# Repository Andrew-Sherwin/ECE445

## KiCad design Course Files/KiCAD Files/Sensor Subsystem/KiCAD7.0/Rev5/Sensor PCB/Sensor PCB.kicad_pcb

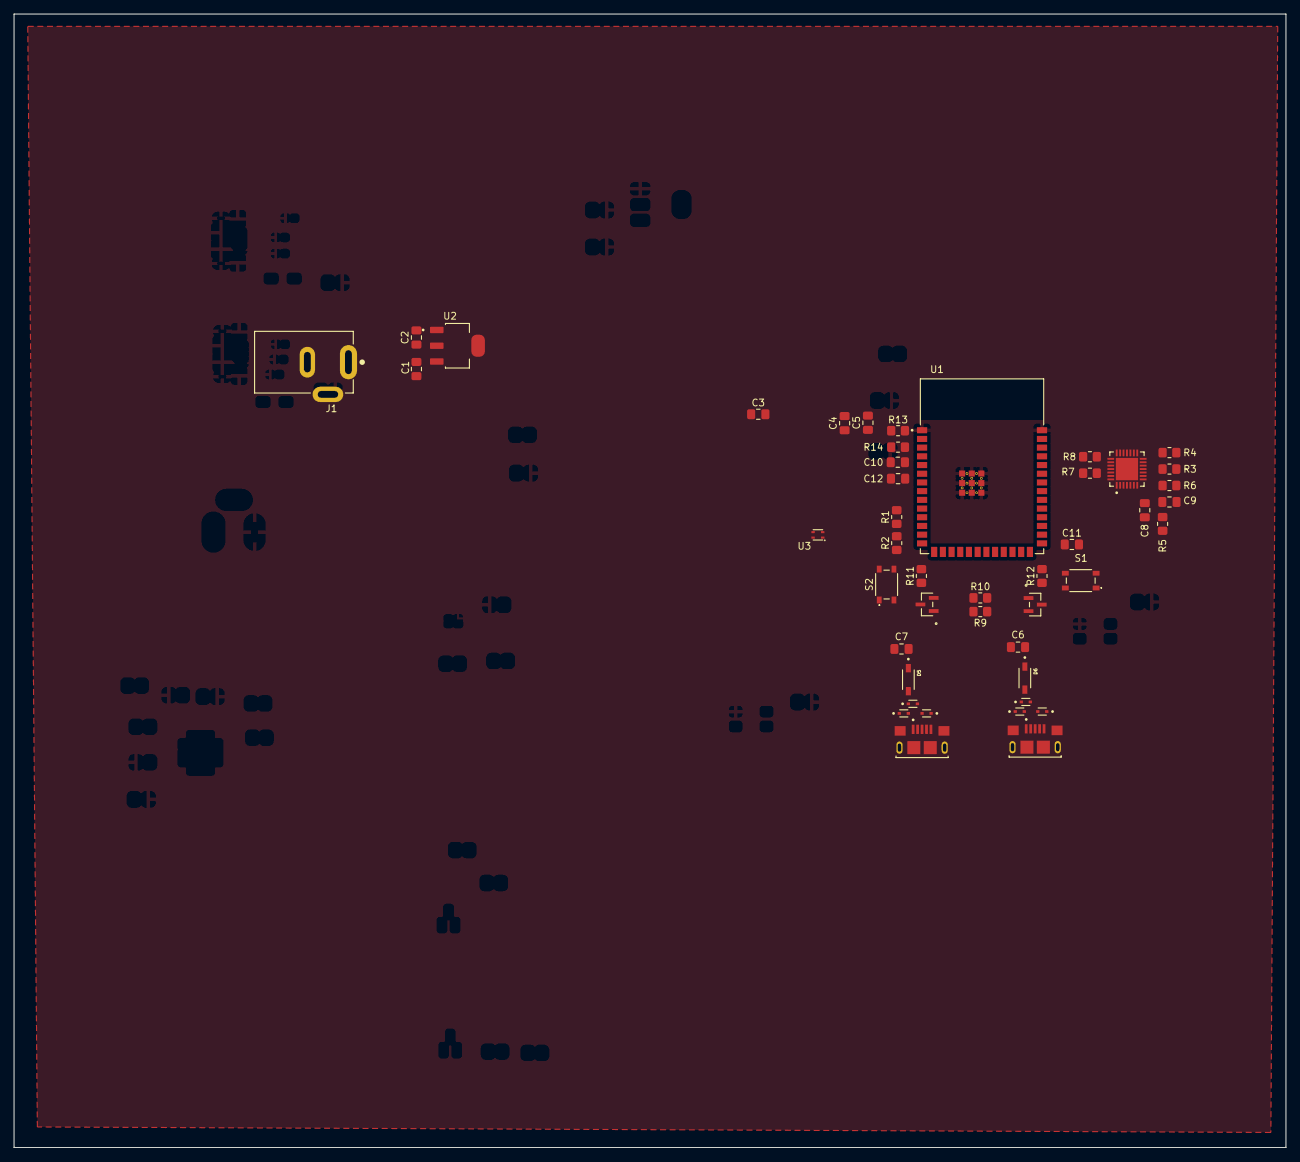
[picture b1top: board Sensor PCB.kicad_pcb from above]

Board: 2 copper layers, 185.6 x 165.4 mm, 45 parts (0 on the bottom side), 28 nets, no tracks yet.

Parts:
C1, C9, C10: 1uF; C_0805_2012Metric_Pad1.18x1.45mm_HandSolder
C2: 4.7uF; C_0805_2012Metric_Pad1.18x1.45mm_HandSolder
C3: 100nF; C_0805_2012Metric_Pad1.18x1.45mm_HandSolder
C4, C6, C7, C8: 10uF; C_0805_2012Metric_Pad1.18x1.45mm_HandSolder
C5, C11, C12: 0.1uF; C_0805_2012Metric_Pad1.18x1.45mm_HandSolder
D1, D2, D3, D4, D7, D8: LESD5D5.0CT1G; LESD5D5_0CT1G
D5, D6: 1N5819HW-7-F
J1: PJ-202AH
J2, J3: 10118193-0001LF
R1, R2, R4, R9, R10, R14: 10000; R_0805_2012Metric_Pad1.20x1.40mm_HandSolder
R3: 1000; R_0805_2012Metric_Pad1.20x1.40mm_HandSolder
R5: 22100; R_0805_2012Metric_Pad1.20x1.40mm_HandSolder
R6: 47500; R_0805_2012Metric_Pad1.20x1.40mm_HandSolder
R7, R8, R11, R12, R13: 0; R_0805_2012Metric_Pad1.20x1.40mm_HandSolder
S1, S2: PTS815_SJG_250_SMTR_LFS; PTS815 SJG 250 SMTR LFS
U1: ESP32-S3-WROOM-1-N8; ESP32-S3-WROOM-1-N8-SnapEDA
U2: LDL1117S33R-SnapEDA
U3: SHT45-AD1B-R3
U4: CP2102N-A02-GQFN28
U5, U6: L8050QLT1G; SOT-23_ONS

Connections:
+3.3V: C2.1, C3.2, C4.1, C5.1, C8.1, R1.2, R2.2, R3.1, R13.2, U2.2 (VOUT), U2.4 (VOUT), U3.3 (VDD), U4.6 (VDD), U4.7 (VREGIN)
+12V: C1.1, J1.1, U2.3 (VIN)
CHIP_PU: C10.1, C12.1, R11.2, R14.2, S2.4 (NO), U1.3 (EN)
DTR: R9.1, U4.28 (DTR), U6.2 (EMITTER)
ESP_3V3: R13.1, R14.1, U1.2 (3V3)
GND: C1.2, C2.2, C3.1, C4.2, C5.2, C6.2, C7.2, C8.2, C9.2, C10.2, C11.2, C12.2, D1.1, D2.1, D3.1, D4.1, D7.1, D8.1, J1.2, J2.5 (GND), J2.S1 (SHIELD), J2.S2 (SHIELD__1), J2.S3 (SHIELD__2), J2.S4 (SHIELD__3), J2.S5 (SHIELD__4), J2.S6 (SHIELD__5), J3.5 (GND), J3.S1 (SHIELD), J3.S2 (SHIELD__1), J3.S3 (SHIELD__2), J3.S4 (SHIELD__3), J3.S5 (SHIELD__4), J3.S6 (SHIELD__5), R4.1, R6.1, S1.1 (COM), S2.1 (COM), U1.1 (GND), U1.40 (GND), U1.41_1 (GND), U1.41_2 (GND), U1.41_3 (GND), U1.41_4 (GND), U1.41_5 (GND), U1.41_6 (GND), U1.41_7 (GND), U1.41_8 (GND), U1.41_9 (GND), U2.1 (GND), U3.4 (VSS), U4.3 (GND), U4.29 (GND__1)
IO0: C11.1, R12.2, S1.4 (NO), U1.27 (IO0)
IO19: D4.2, J3.2 (D-), U1.13 (IO19)
IO20: D3.2, J3.3 (D+), U1.14 (IO20)
unnamed: C6.1, D6.C
unnamed: C7.1, D5.C
unnamed: R1.1, U1.12 (IO8), U3.1 (SDA)
unnamed: R2.1, U1.17 (IO9), U3.2 (SCL)
unnamed: R8.1, U4.25 (RXD)
unnamed: R7.1, U4.26 (TXD)
unnamed: C9.1, R5.2, R6.2, U4.8 (VBUS)
unnamed: R3.2, U4.9 (~RST)
unnamed: R4.2, U4.11 (~SUSPEND)
unnamed: R9.2, U5.1 (BASE)
unnamed: R11.1, U5.3 (COLLECTOR)
unnamed: R10.2, U6.1 (BASE)
unnamed: R12.1, U6.3 (COLLECTOR)
RTS: R10.1, U4.24 (RTS), U5.2 (EMITTER)
U0RXD: R7.2, U1.36 (RXD0)
U0TXD: R8.2, U1.37 (TXD0)
USB_DN: D2.2, J2.2 (D-), U4.5 (D-)
USB_DP: D1.2, J2.3 (D+), U4.4 (D+)
VBUS: D5.A, D6.A, D7.2, D8.2, J2.1 (VUSB), J3.1 (VUSB), R5.1

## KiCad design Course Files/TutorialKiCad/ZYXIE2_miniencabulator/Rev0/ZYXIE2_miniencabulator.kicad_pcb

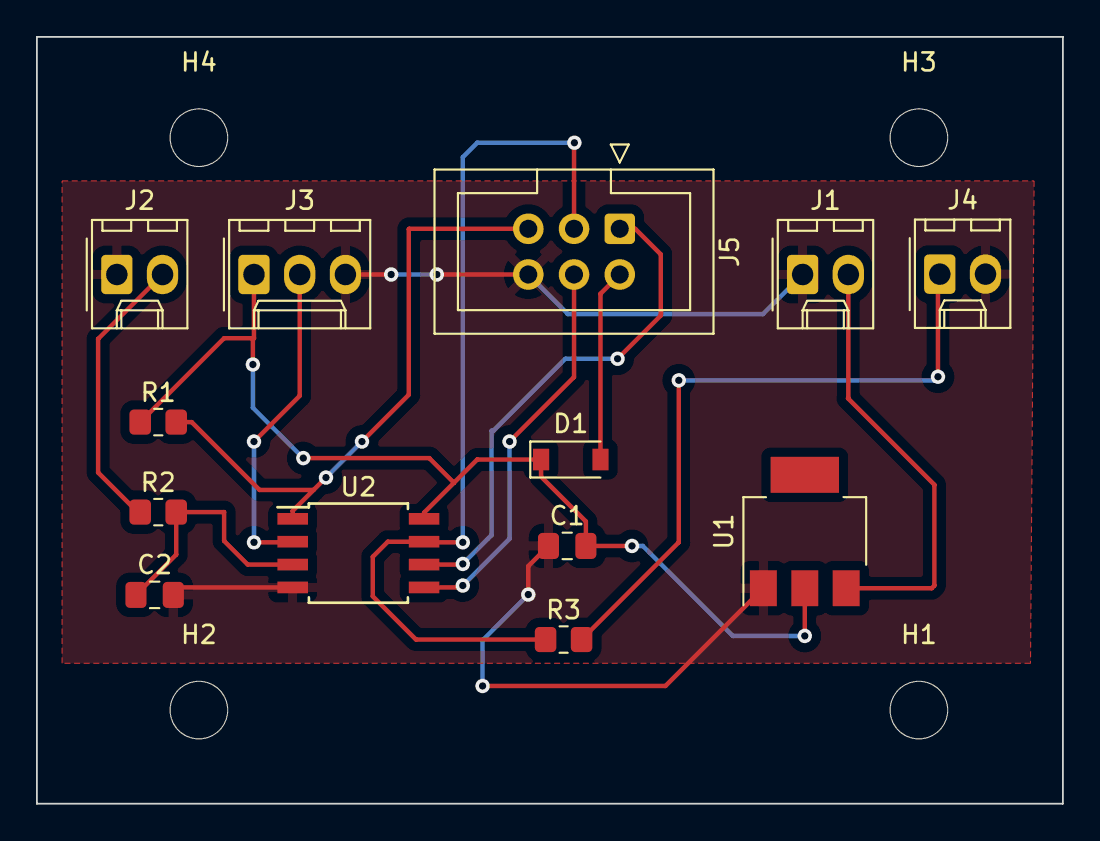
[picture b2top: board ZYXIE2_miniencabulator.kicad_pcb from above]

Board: 2 copper layers, 57.0 x 42.6 mm, 17 parts (0 on the bottom side), 12 nets.

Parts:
C1, C2: 1uF; C_0805_2012Metric_Pad1.18x1.45mm_HandSolder
D1: MBR0520; D_SOD-123
H1, H2, H3, H4: MountingHole; MountingHole_3.2mm_M3
J1: Vin; Molex_KK-254_AE-6410-02A_1x02_P2.54mm_Vertical
J2: BUTTON; Molex_KK-254_AE-6410-02A_1x02_P2.54mm_Vertical
J3: POT; Molex_KK-254_AE-6410-03A_1x03_P2.54mm_Vertical
J4: LED; Molex_KK-254_AE-6410-02A_1x02_P2.54mm_Vertical
J5: AVR-ISP-6; IDC-Header_2x03_P2.54mm_Vertical
R1, R2: 10000; R_0805_2012Metric_Pad1.20x1.40mm_HandSolder
R3: 1000; R_0805_2012Metric_Pad1.20x1.40mm_HandSolder
U1: LM1117-5.0; SOT-223
U2: ATtiny85-20S; SOIC-8W_5.3x5.3mm_P1.27mm

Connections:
+5V: C1.2, D1.1 (K), J3.1, R1.1, U1.2 (VO), U2.8 (VCC)
/MISO: J5.1 (MISO), U2.6 (PB1)
/MOSI: J5.4 (MOSI), U2.5 (AREF/PB0)
/RST: J5.5 (~RST), R1.2, U2.1 (~RESET/PB5)
/SCK: J5.3 (SCK), R3.1, U2.7 (PB2)
/button: C2.1, R2.2, U2.3 (XTAL2/PB4)
GND: C1.1, C2.2, J1.1, J2.1, J3.3, J4.2, J5.6 (GND), U1.1 (GND), U2.4 (GND)
unnamed: D1.2 (A), J5.2 (VCC)
unnamed: J3.2, U2.2 (XTAL1/PB3)
unnamed: J2.2, R2.1
unnamed: J4.1, R3.2
unnamed: J1.2, U1.3 (VI)
